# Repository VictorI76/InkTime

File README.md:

# Proiect Hector Watch - nRF52840 Smartwatch

Acest document conține specificațiile tehnice, Bill of Materials (BOM) și detaliile de design pentru proiectul Hector Watch.

---

# 1. Diagramă Bloc

---

# 2. Bill Of Materials (BOM)

| Cant. | Referințe | Valoare | Descriere Tehnică | Producător | Cod Piesă (MPN) |
|:---:|:---|:---|:---|:---|:---|
| 1 | U1 | nRF52840 | Microcontroller Bluetooth LE, AQFN-73 | Nordic Semi | nRF52840-QIAA |
| 1 | IC1 | BQ25180 | Charger Li-Ion/Polymer, 8-DSBGA | Texas Instr. | BQ25180YBGR |
| 1 | IC2 | DRV2605 | Driver Haptic LRA/ERM, 9-DSBGA | Texas Instr. | DRV2605YZFR |
| 1 | IC3 | BMA421 | Accelerometru Triaxial 12-bit | Bosch | BMA423 |
| 1 | IC9 | RT6160 | Buck-Boost DC-DC Controller, 15-WL-CSP | Richtek | RT6160AWSC |
| 1 | U3 | MAX17048 | Fuel Gauge (Monitorizare Baterie) | Maxim/ADI | MAX17048G+T10 |
| 1 | ANT1 | 2.45GHz | Antenă Chip Ceramică | Johanson | 2450AT18B100E |
| 1 | J4 | USB-C | Conector USB Type-C 16 pini | Kinghelm | KH-TYPE-C-16P |
| 1 | J1 | FPC 24 | Conector FFC/FPC 0.5mm, 24 pini  | Molex | 503480-2400 |
| 1 | J2 | TC2030 | Interfață programare Tag-Connect | Tag-Connect | TC2030-IDC |
| 3 | SW_DN, SW_ENT, SW_UP | Tactile | Butoane navigare interfață | Panasonic | EVP-AKE31A |
| 1 | L5 | 68uH | Inductor putere ecranat | Wurth | 744043680 |
| 1 | L4 | 0.47uH | Inductor SMD | TDK | FTC252012SR47MBCA |
| 1 | L2 | 10uH | Inductor generic 0402 | - | - |
| 1 | L3 | 15nH | Inductor generic 0201 | - | - |
| 1 | L1 | 3.9nH | Inductor generic 0201  | - | - |
| 1 | X1 | 32MHz | Cristal cuarț (Main Clock)  | - | - |
| 1 | X2 | 32.768kHz | Cristal cuarț (RTC Clock)  | - | - |
| 3 | D2, D4, D5 | MBR0530 | Diodă Schottky 0.5A, 30V, SOD-123 | ON Semi | MBR0530 |
| 1 | D3 | USBLC6-2 | Protecție ESD USB, SOT-23-6 | ST Micro | USBLC6-2SC6Y |
| 1 | Q1 | P-Ch | Tranzistor P-channel MOSFET | - | - |
| 1 | Q3 | N-Ch | Tranzistor N-channel MOSFET 30V, 1.5A | Vishay | Si1308EDL |
| 6 | R2_EP_DR, R5-R9, R_PWR | 10K | Rezistență 0201 Thin Film | - | - |
| 2 | R1_USB, R2_USB | 5K1 | Rezistență 0201 Thin Film  | - | - |
| 2 | R17, R18 | 3K3 | Rezistență 0201 Thin Film  | - | - |
| 3 | R2, R3, R4 | 0 | Rezistență 0201 (Jumper/0 Ohm) | - | - |
| 6 | C5-C19 | 100nF | Condensator decuplare 0201 | - | - |
| 9 | EPD_C1-C12 | 1uF/50V | Condensator 0402 | - | - |
| 5 | C6, C14, C20, C21, C43 | 4.7uF | Condensator 0402  | - | - |
| 3 | C1-EP-DR, C24, C39 | 10uF | Condensator 0402 | - | - |
| 2 | C25, C33 | 22uF | Condensator 0402 | - | - |
| 4 | C23, C27, C34, C42 | 0.1uF | Condensator 0201 | - | - |
| 4 | C1, C2, C17, C18 | 12pF | Condensator 0201 | - | - |
| 14 | TP_3.3V ... TP_VREG | Test Pad | Puncte de testare semnale | - | - |
| 1 | SJ1 | Solder | Jumper de lipit SMD | - | - |

---

# 3. Funcționalității Hardware

## Descrierea Detaliată a Funcționalității Hardware

Proiectul Hector Watch utilizează o arhitectură modulară optimizată pentru eficiență energetică și dimensiuni reduse, având la bază următoarele componente principale:

### 1. Unitatea Centrală de Procesare (MCU)
* **nRF52840 (U1)**: Acesta este un System-on-Chip (SoC) avansat care rulează logica principală a ceasului și gestionează stack-ul Bluetooth Low Energy.
* **Rol**: Controlează comunicația cu toți senzorii prin magistrala **I2C** și interfața digitală pentru display.

### 2. Managementul Puterii (Power Management)
Sistemul de alimentare este proiectat pentru a asigura stabilitate și longevitate bateriei Li-Ion:
* **Încărcător BQ25180 (IC1)**: Gestionează procesul de încărcare a bateriei via USB și include protecții integrate pentru celula de litiu.
* **Regulator Buck-Boost RT6160 (IC9)**: Un convertor DC-DC care stabilizează tensiunea de sistem la 3.3V, indiferent de variațiile tensiunii bateriei.
* **Monitor Baterie MAX17048 (U3)**: Un circuit de tip "Fuel Gauge" care utilizează algoritmul ModelGauge pentru a raporta precis starea de încărcare a bateriei.

## Analiza Consumului de Energie și Autonomie

Pentru a estima durata de viață a bateriei, am analizat principalele stări de funcționare ale componentelor identificate în BOM:

### 1. Consum pe Module (Estimativ)

| Modul / Componentă | Deep Sleep / Standby | Operare Activă (Typical) |
| :--- | :--- | :--- |
| **nRF52840 (U1)** | ~1.5 µA (RTC ON) | ~4.8 mA |
| **BMA421 (IC3)** | ~1 µA (Suspend) | ~14.5 µA (Low Power) |
| **MAX17048 (U3)** | ~3 µA (Hibernate) | ~23 µA (Activ) |
| **RT6160 (IC9)** | ~1 µA (Iq) | Eficiență >85% |
| **Display E-Paper** | **0 µA** (Static) | ~2-8 mA (Refresh doar) |

### 2. Scenariu de Utilizare Tipic
Consumul mediu este calculat pe baza unui ciclu de funcționare (Duty Cycle) în care dispozitivul petrece 99% din timp în mod Sleep:

* **Consum în Sleep (Sistem complet):** ~20 µA (micro-Amperi).
* **Consum în Activitate (Scurte pulsații):** ~5-10 mA (mili-Amperi).
* **Consum Mediu Estimat:** **~55 µA**.

## Calcul Autonomie
Considerând o baterie Li-Ion standard de **200 mAh**:

$$Autonomie (ore) = \frac{Capacitate (mAh)}{Consum Mediu (mA)}$$

$$Autonomie = \frac{200 mAh}{0.055 mA} \approx 3636 \text{ ore}$$

**Rezultat:** Dispozitivul poate funcționa teoretic aproximativ **5 luni** cu o singură încărcare în regim de standby/notificări ocazionale. Utilizarea intensă a motorului haptic (DRV2605) sau refresh-ul frecvent al ecranului va reduce această perioadă la aproximativ **2-4 săptămâni**.

### 3. Senzori și Feedback Haptic
* **Accelerometru BMA421/BMA423 (IC3)**: Senzor de mișcare triaxial cu consum ultra-redus, utilizat pentru pedometru și detecția gesturilor de ridicare a mâinii.
* **Driver Haptic DRV2605 (IC2)**: Controller specializat pentru motoare de vibrație (ERM/LRA) ce oferă o bibliotecă internă de efecte tactile complexe.

### 4. Interfețe și Comunicație
* **Antenă Chip 2.45GHz (ANT1)**: Componentă ceramică acordată pentru frecvența Bluetooth, esențială pentru conexiunea wireless.
* **Conector FPC J1 (24 pini)**: Interfață de 0.5mm utilizată pentru conectarea panoului de afișaj E-Paper.
* **Port USB Type-C (J4)**: Punctul principal de alimentare și încărcare a dispozitivului.
* **Butoane (SW_UP, SW_DN, SW_ENT)**: Trei switch-uri tactice pentru navigarea utilizatorului în meniurile ceasului.

### 5. Protecție și Componente Pasive
* **Protecție ESD USBLC6-2SC6Y (D3)**: Protejează pinii de date USB împotriva descărcărilor electrostatice.
* **Diodă Schottky MBR0530 (D2, D4, D5)**: Componente utilizate pentru redresare și protecția căilor de alimentare.
* **Filtrare locală**: Sistemul utilizează o rețea densă de condensatoare de decuplare (majoritatea în capsulă 0201) pentru a reduce zgomotul electric pe liniile de alimentare.
---

# 4. Alocare Pini nRF52840

## 1. Alimentare și stabilizare

### Pini implicați

* VDD, VDDH
* DEC1, DEC3, DEC4, DEC5, DEC6
* DCC, DCCHP
* VSS (GND)

### Conectare

* VDD este conectat la 3.3V
* VDDH este conectat la sursa principală (baterie sau regulator)
* Pinii DEC sunt conectați la condensatori (100nF, 1µF, 4.7µF) către masă
* DCC și DCCHP sunt conectați la inductoare pentru convertorul DC/DC

### Motivație

* Asigură stabilitatea tensiunilor interne
* Reduce zgomotul electric
* Permite funcționarea eficientă energetic prin utilizarea convertorului DC/DC intern

---

## 2. Interfața RF (2.4 GHz)

### Pini implicați

* ANT
* VSS_PA

### Conectare

* ANT este conectat la o rețea de adaptare (matching network) formată din inductoare și condensatori
* Rețeaua este conectată la antenă

### Motivație

* Adaptarea impedanței la 50 ohmi
* Maximizarea puterii semnalului emis
* Creșterea sensibilității la recepție

---

## 3. Oscilatoare (ceas)

### Pini implicați

* P0.00 (XL1)
* P0.01 (XL2)
* XC1, XC2

### Conectare

* Cristal de 32.768 kHz cu condensatori de 12pF
* Cristal de 32.768 MHz

### Motivație

* Ceasul de 32 kHz este utilizat pentru RTC și moduri low-power
* Ceasul de mare frecvență este necesar pentru comunicații radio precise

---

## 4. Debug și programare (SWD)

### Pini implicați

* SWDIO
* SWDCLK
* RESET
* SWO (opțional)

### Conectare

* Conectați la un header de programare (TC2030)
* Expuse și prin puncte de test

### Motivație

* Programarea firmware-ului
* Debugging în timpul dezvoltării

---

## 5. Interfață USB

### Pini implicați

* D+
* D-
* VBUS

### Conectare

* Conectați la conector USB-C
* Include protecție ESD

### Motivație

* Comunicație USB cu alte dispozitive
* Posibilitate de alimentare prin USB

---

## 6. Interfață SPI – Display E-Paper

### Pini implicați

* MOSI
* SCK
* EPD_CS
* EPD_DC
* EPD_RST
* EPD_BUSY

### Conectare

* Conectați la conectorul display-ului și circuitul de comandă

### Motivație

* SPI oferă comunicație rapidă
* Liniile suplimentare controlează funcționarea display-ului (comenzi, reset, status)

---

## 7. Interfață I2C

### Pini implicați

* SDA
* SCL

### Conectare

* Conectați la:

  * IMU (accelerometru)
  * Fuel gauge
  * Driver haptic
* Include rezistențe de pull-up (~3.3kΩ)

### Motivație

* Permite conectarea mai multor dispozitive pe aceeași magistrală
* Reduce numărul de pini necesari

---

## 8. GPIO și semnale de întrerupere

### Exemple de semnale

* IMU_INT1, IMU_INT2
* PMIC_INT
* HAPTIC_EN
* Butoane

### Conectare

* Intrări/ieșiri digitale configurabile

### Motivație

* Gestionarea evenimentelor asincrone
* Permite funcționare eficientă energetic (bazată pe întreruperi)

---

## 9. Alimentare externă și baterie

### Conectare

* VBUS → USB
* VBAT → baterie LiPo
* Conectate la:

  * Circuit de încărcare
  * Circuit de monitorizare (fuel gauge)

### Motivație

* Management complet al energiei
* Separarea funcțiilor de alimentare și monitorizare

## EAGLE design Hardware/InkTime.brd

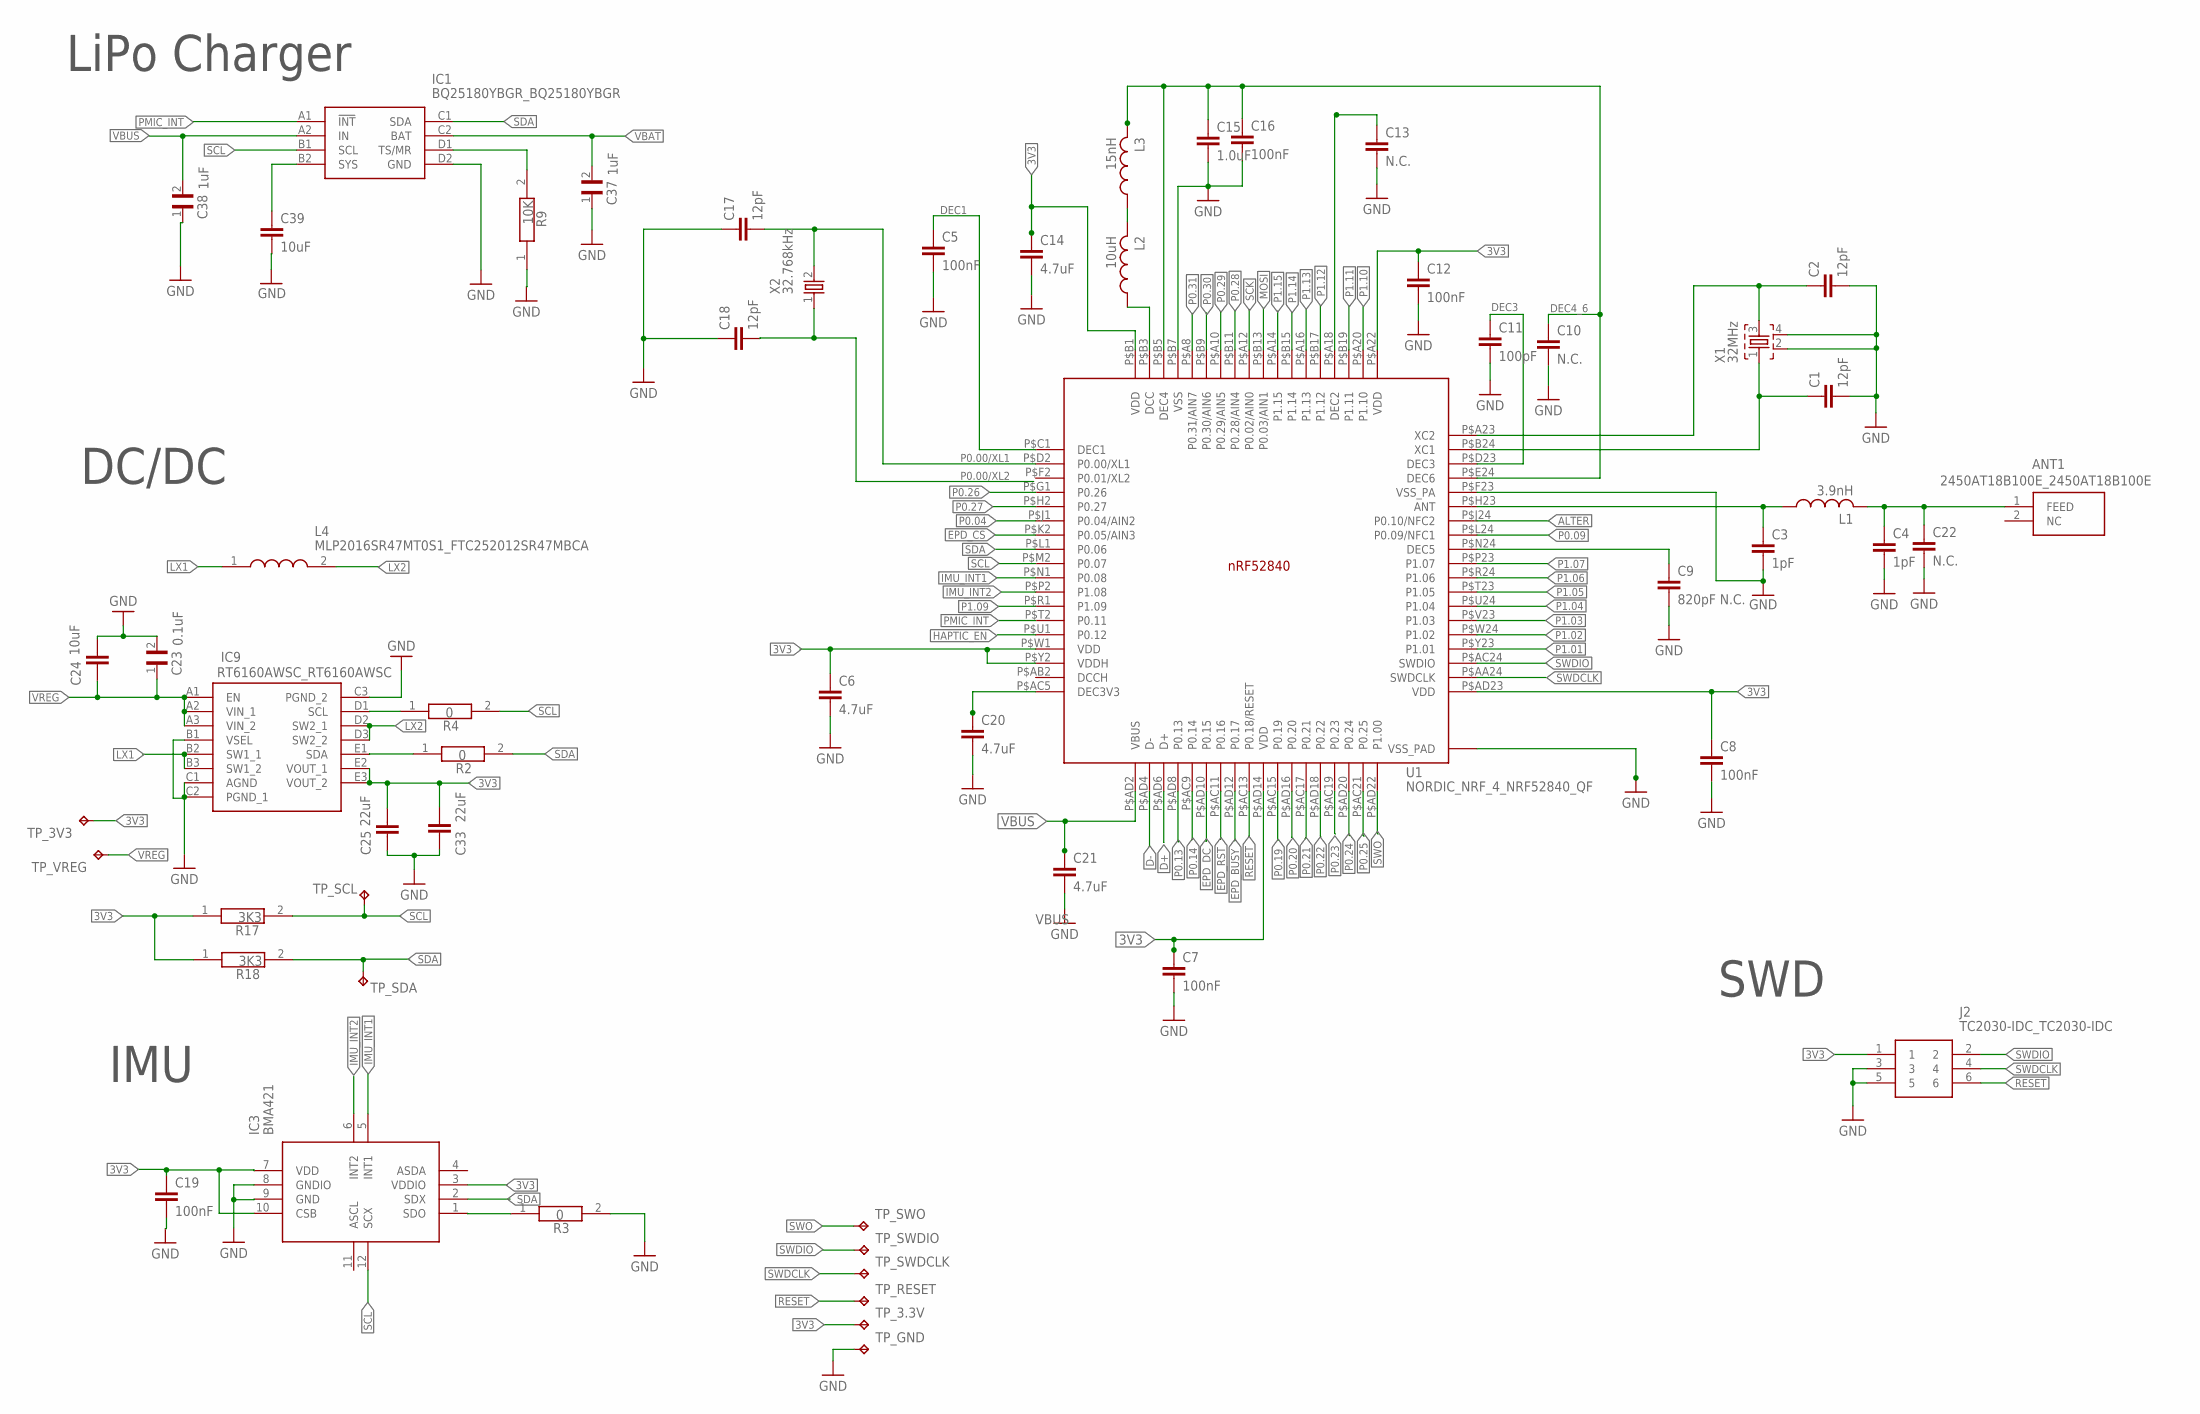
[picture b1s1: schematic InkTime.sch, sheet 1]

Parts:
ANT1: 2450AT18B100E_2450AT18B100E; 2450AT18B100E_ANTC3216X140N
C1, C2, C17, C18: 12pF; NORDIC_NRF_3_RESC0201_N
C3, C4: 1pF; NORDIC_NRF_3_RESC0201_N
C5, C7, C8, C12, C16, C19: 100nF; NORDIC_NRF_3_RESC0201_N
C6, C14, C20, C21: 4.7uF; NORDIC_NRF_3_RESC0402_N
C9: 820pF N.C.; NORDIC_NRF_3_RESC0201_N
C10: N.C.; NORDIC_NRF_3_RESC0402_N
C11: 100pF; NORDIC_NRF_3_RESC0201_N
C13, C22: N.C.; NORDIC_NRF_3_RESC0201_N
C15: 1.0uF; NORDIC_NRF_3_RESC0402_N
C23: 0.1uF; GRM011R60J152KE01L_2_CAPC0201X13N
C24, C39: 10uF; NORDIC_NRF_3_RESC0402_N
C25, C33: 22uF; NORDIC_NRF_3_RESC0402_N
C37, C38: 1uF; GRM011R60J152KE01L_2_CAPC0201X13N
IC1: BQ25180YBGR_BQ25180YBGR; BQ25180YBGR_BGA8C40P2X4_100X155X50
IC3: BMA421; BMA423_BMA423
IC9: RT6160AWSC_RT6160AWSC; RT6160AWSC_BGA15C40P3X5_140X230X60
J2: TC2030-IDC_TC2030-IDC; TC2030-IDC_TC2030IDC
L1: 3.9nH; NORDIC_NRF_2_RESC0201_N
L2: 10uH; NORDIC_NRF_2_RESC0402_N
L3: 15nH; NORDIC_NRF_2_RESC0201_N
L4: MLP2016SR47MT0S1_FTC252012SR47MBCA; MLP2016SR47MT0S1_INDC2016X100N
R2, R3, R4: 0; CPF0201D7K68C1_0201
R9: 10K; CPF0201D7K68C1_0201
R17, R18: 3K3; CPF0201D7K68C1_0201
TP_3.3V, TP_3V3: HECTOR_WATCH_1_TPTP20R; HECTOR_WATCH_1_TP20R
TP_GND: HECTOR_WATCH_1_TPTP20R; HECTOR_WATCH_1_TP20R
TP_RESET: HECTOR_WATCH_1_TPTP20R; HECTOR_WATCH_1_TP20R
TP_SCL: HECTOR_WATCH_1_TPTP20R; HECTOR_WATCH_1_TP20R
TP_SDA: HECTOR_WATCH_1_TPTP20R; HECTOR_WATCH_1_TP20R
TP_SWDCLK: HECTOR_WATCH_1_TPTP20R; HECTOR_WATCH_1_TP20R
TP_SWDIO: HECTOR_WATCH_1_TPTP20R; HECTOR_WATCH_1_TP20R
TP_SWO: HECTOR_WATCH_1_TPTP20R; HECTOR_WATCH_1_TP20R
TP_VREG: HECTOR_WATCH_1_TPTP20R; HECTOR_WATCH_1_TP20R
U1: NORDIC_NRF_4_NRF52840_QF; NORDIC_NRF_4_AQFN50P700X700X85_HS-74N
X1: 32MHz; NORDIC_NRF_BT-XTAL_2016_N
X2: 32.768kHz; NORDIC_NRF_1_XTAL_3215_N

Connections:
3V3: C6.1, C7.1, C8.1, C12.1, C14.1, C19.1, C25.1, C33.1, IC3.3 (VDDIO), IC3.7 (VDD), IC3.10 (CSB), IC9.E2 (VOUT_1), IC9.E3 (VOUT_2), J2.1, R17.1, R18.1, TP_3.3V.TP, TP_3V3.TP, U1.P$A22 (VDD), U1.P$AD14 (VDD), U1.P$AD23 (VDD), U1.P$B1 (VDD), U1.P$W1 (VDD); also elsewhere on the board
ALTER: U1.P$J24 (P0.10/NFC2); also elsewhere on the board
D+: U1.P$AD6 (D+); also elsewhere on the board
D-: U1.P$AD4 (D-); also elsewhere on the board
DEC1: C5.1, U1.P$C1 (DEC1)
DEC2: C13.1, U1.P$A18 (DEC2)
DEC3: C11.1, U1.P$D23 (DEC3)
DEC4_6: C10.1, C15.1, C16.1, L3.2, U1.P$B5 (DEC4), U1.P$E24 (DEC6)
EPD_BUSY: U1.P$AD12 (P0.17); also elsewhere on the board
EPD_CS: U1.P$K2 (P0.05/AIN3); also elsewhere on the board
EPD_DC: U1.P$AD10 (P0.15); also elsewhere on the board
EPD_RST: U1.P$AC11 (P0.16); also elsewhere on the board
GND: C1.2, C2.2, C3.2, C4.2, C5.2, C6.2, C7.2, C8.2, C9.2, C10.2, C11.2, C12.2, C13.2, C14.2, C15.2, C16.2, C17.1, C18.1, C19.2, C20.2, C21.2, C22.2, C23.2, C24.1, C25.2, C33.2, C37.1, C38.1, C39.2, IC1.D2 (GND), IC3.8 (GNDIO), IC3.9 (GND), IC9.B1 (VSEL), IC9.C1 (AGND), IC9.C2 (PGND_1), IC9.C3 (PGND_2), J2.3, J2.5, R3.2, R9.1, TP_GND.TP, U1.P$74 (VSS_PAD), U1.P$75 (VSS_PAD), U1.P$76 (VSS_PAD), U1.P$77 (VSS_PAD), U1.P$78 (VSS_PAD), U1.P$79 (VSS_PAD), U1.P$80 (VSS_PAD), U1.P$81 (VSS_PAD), U1.P$82 (VSS_PAD), U1.P$83 (VSS_PAD), U1.P$84 (VSS_PAD), U1.P$85 (VSS_PAD), U1.P$86 (VSS_PAD), U1.P$87 (VSS_PAD), U1.P$88 (VSS_PAD), U1.P$89 (VSS_PAD), U1.P$90 (VSS_PAD), U1.P$B7 (VSS), U1.P$F23 (VSS_PA), X1.2, X1.4; also elsewhere on the board
HAPTIC_EN: U1.P$U1 (P0.12); also elsewhere on the board
IMU_INT1: IC3.5 (INT1), U1.P$N1 (P0.08)
IMU_INT2: IC3.6 (INT2), U1.P$P2 (P1.08)
LX1: IC9.B2 (SW1_1), IC9.B3 (SW1_2), L4.1
LX2: IC9.D2 (SW2_1), IC9.D3 (SW2_2), L4.2
MOSI: U1.P$B13 (P0.03/AIN1); also elsewhere on the board
unnamed: L2.2, L3.1
unnamed: C20.1, U1.P$AC5 (DEC3V3)
unnamed: L2.1, U1.P$B3 (DCC)
unnamed: C3.1, L1.1, U1.P$H23 (ANT)
unnamed: C9.1, U1.P$N24 (DEC5)
unnamed: C2.1, U1.P$A23 (XC2), X1.3
unnamed: ANT1.1 (FEED), C4.1, C22.1, L1.2
unnamed: C1.1, U1.P$B24 (XC1), X1.1
unnamed: IC9.D1 (SCL), R4.1
unnamed: IC9.E1 (SDA), R2.1
unnamed: C39.1, IC1.B2 (SYS)
unnamed: IC1.D1 (TS/MR), R9.2
unnamed: IC3.1 (SDO), R3.1
P0.00/XL1: C17.2, U1.P$D2 (P0.00/XL1), X2.2
P0.00/XL2: C18.2, X2.1
P0.04: U1.P$J1 (P0.04/AIN2)
P0.09: U1.P$L24 (P0.09/NFC1)
P0.13: U1.P$AD8 (P0.13); also elsewhere on the board
P0.14: U1.P$AC9 (P0.14); also elsewhere on the board
P0.19: U1.P$AC15 (P0.19)
P0.20: U1.P$AD16 (P0.20)
P0.21: U1.P$AC17 (P0.21)
P0.22: U1.P$AD18 (P0.22)
P0.23: U1.P$AC19 (P0.23)
P0.24: U1.P$AD20 (P0.24)
P0.25: U1.P$AC21 (P0.25)
P0.26: U1.P$G1 (P0.26)
P0.27: U1.P$H2 (P0.27)
P0.28: U1.P$B11 (P0.28/AIN4)
P0.29: U1.P$A10 (P0.29/AIN5)
P0.30: U1.P$B9 (P0.30/AIN6)
P0.31: U1.P$A8 (P0.31/AIN7)
P1.01: U1.P$Y23 (P1.01); also elsewhere on the board
P1.02: U1.P$W24 (P1.02); also elsewhere on the board
P1.03: U1.P$V23 (P1.03)
P1.04: U1.P$U24 (P1.04)
P1.05: U1.P$T23 (P1.05)
P1.06: U1.P$R24 (P1.06)
P1.07: U1.P$P23 (P1.07)
P1.09: U1.P$R1 (P1.09)
P1.10: U1.P$A20 (P1.10)
P1.11: U1.P$B19 (P1.11)
P1.12: U1.P$B17 (P1.12)
P1.13: U1.P$A16 (P1.13)
P1.14: U1.P$B15 (P1.14)
P1.15: U1.P$A14 (P1.15)
PMIC_INT: IC1.A1 (!INT), U1.P$T2 (P0.11)
RESET: J2.6, TP_RESET.TP, U1.P$AC13 (P0.18/RESET); also elsewhere on the board
SCK: U1.P$A12 (P0.02/AIN0); also elsewhere on the board
SCL: IC1.B1 (SCL), IC3.12 (SCX), R4.2, R17.2, TP_SCL.TP, U1.P$M2 (P0.07); also elsewhere on the board
SDA: IC1.C1 (SDA), IC3.2 (SDX), R2.2, R18.2, TP_SDA.TP, U1.P$L1 (P0.06); also elsewhere on the board
SWDCLK: J2.4, TP_SWDCLK.TP, U1.P$AA24 (SWDCLK)
SWDIO: J2.2, TP_SWDIO.TP, U1.P$AC24 (SWDIO)
SWO: TP_SWO.TP, U1.P$AD22 (P1.00)
VBAT: C37.2, IC1.C2 (BAT); also elsewhere on the board
VBUS: C21.1, C38.2, IC1.A2 (IN), U1.P$AD2 (VBUS); also elsewhere on the board
VREG: C23.1, C24.2, IC9.A1 (EN), IC9.A2 (VIN_1), IC9.A3 (VIN_2), TP_VREG.TP

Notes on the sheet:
SWD
IMU
DC/DC
LiPo Charger

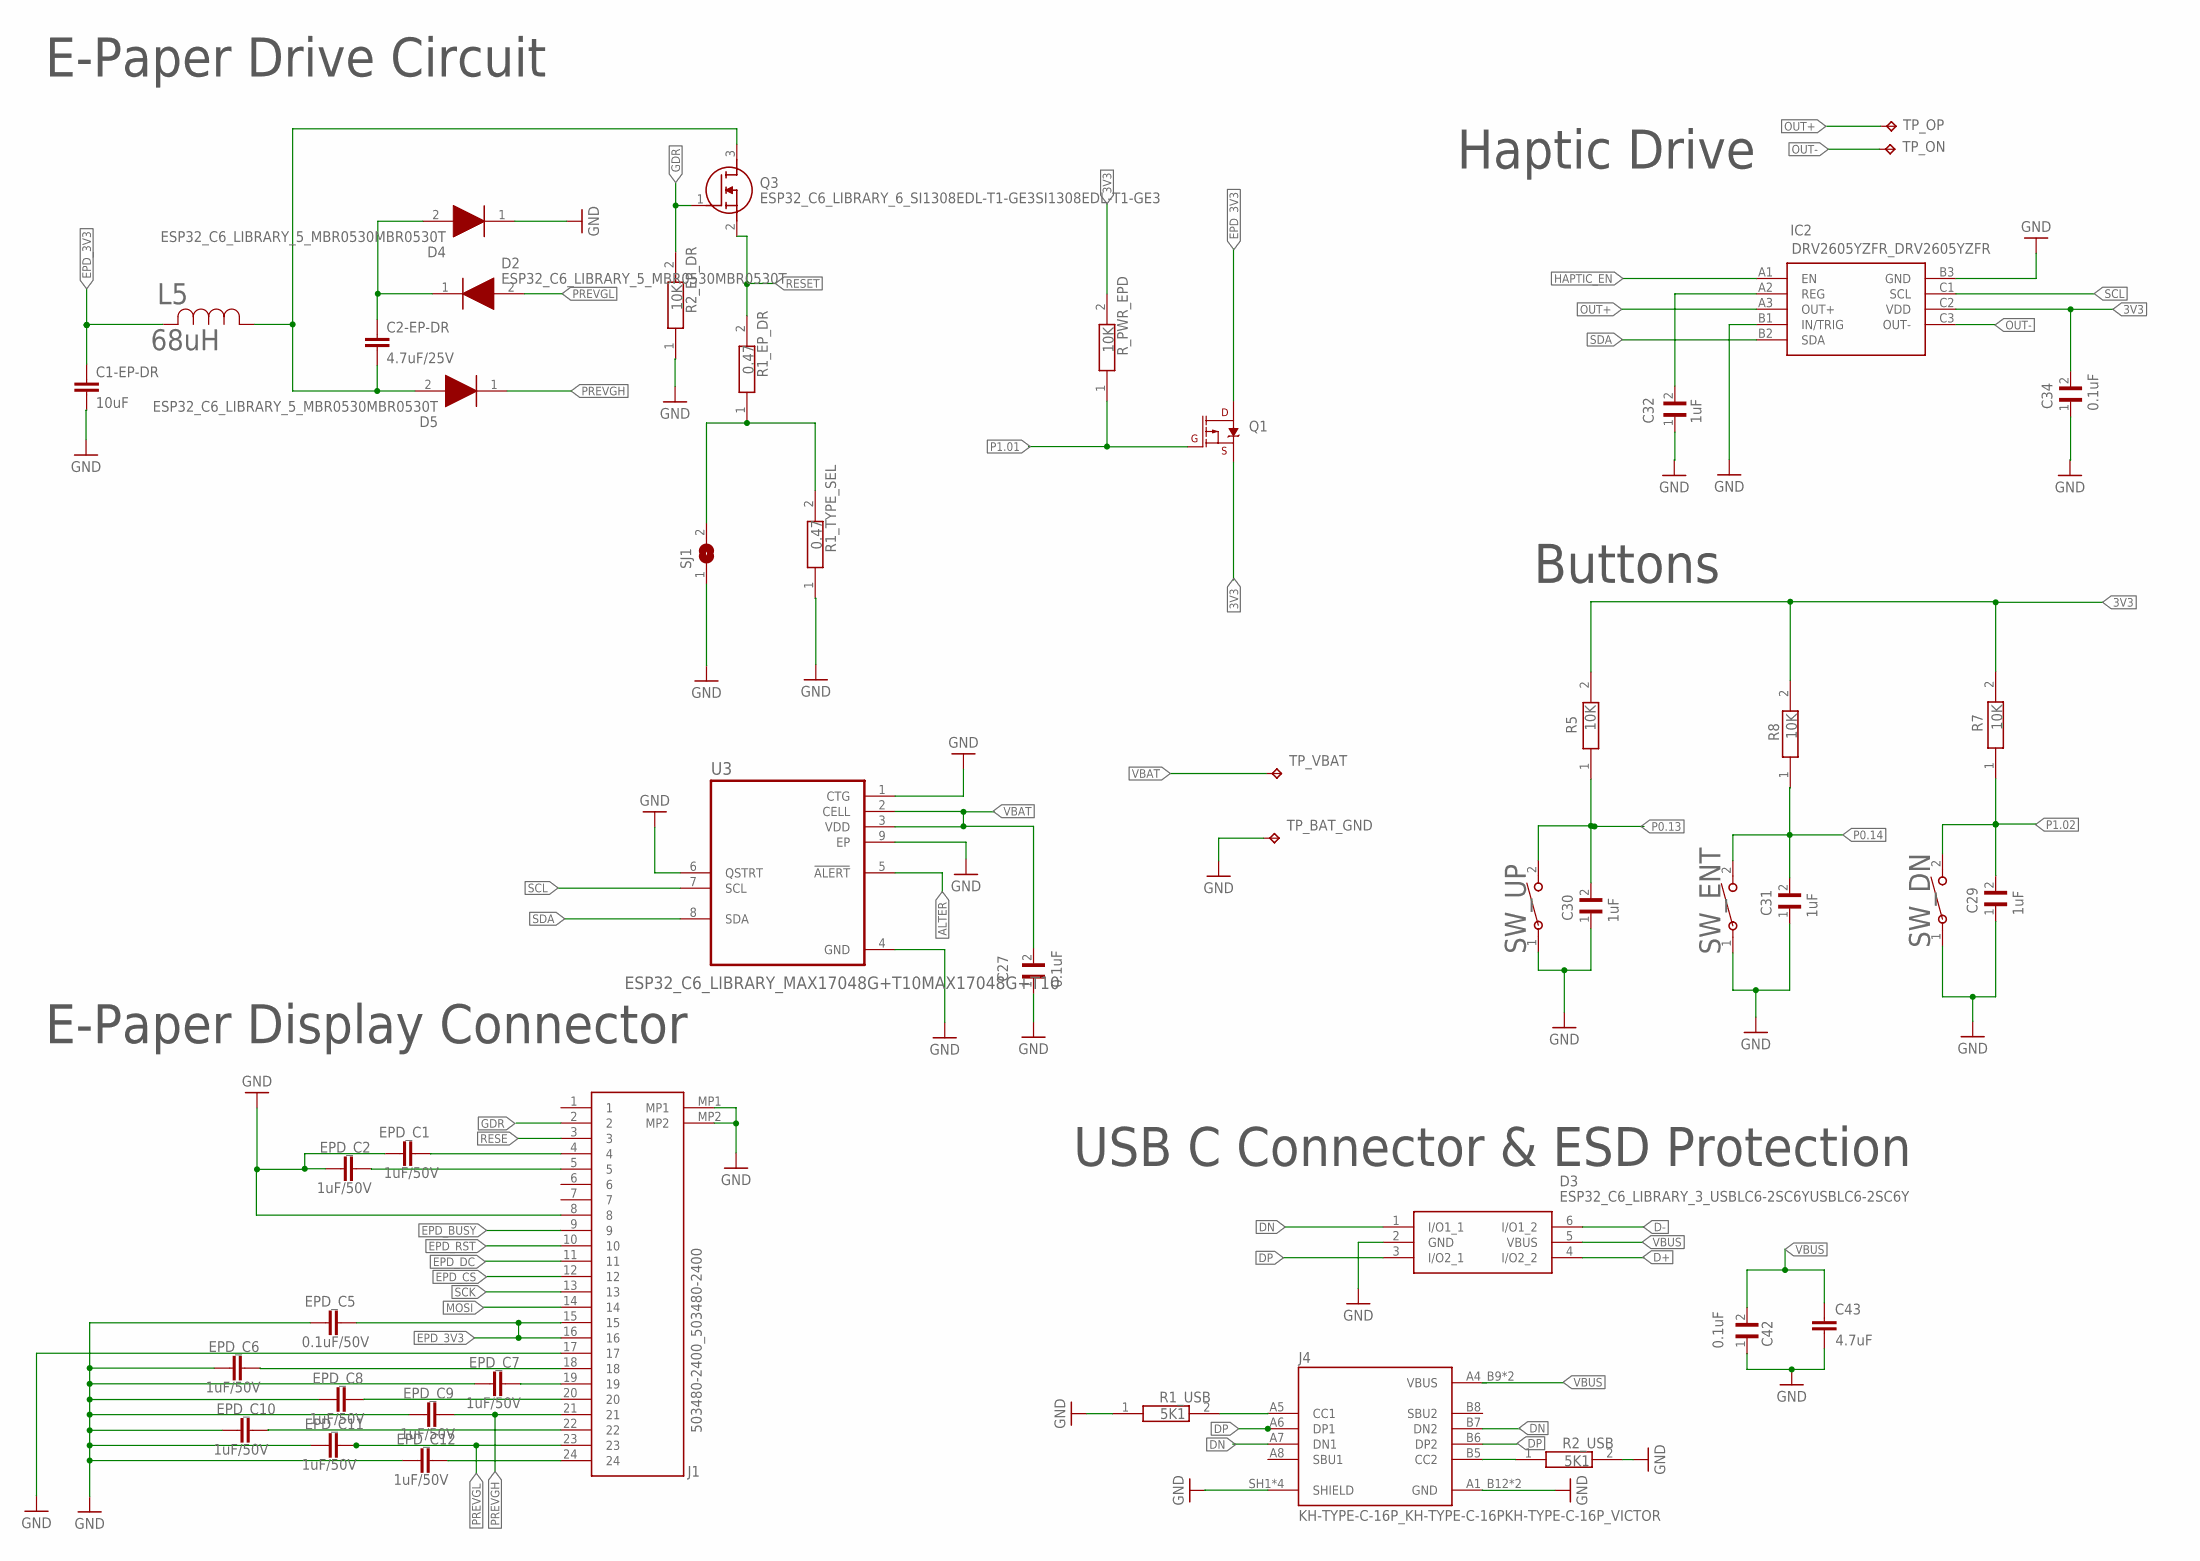
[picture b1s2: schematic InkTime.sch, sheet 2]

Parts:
C1-EP-DR: 10uF; NORDIC_NRF_3_RESC0402_N
C2-EP-DR: 4.7uF/25V; NORDIC_NRF_3_RESC0201_N
C27, C34, C42: 0.1uF; GRM011R60J152KE01L_2_CAPC0201X13N
C29, C30, C31, C32: 1uF; GRM011R60J152KE01L_2_CAPC0201X13N
C43: 4.7uF; NORDIC_NRF_3_RESC0402_N
D2, D4, D5: ESP32_C6_LIBRARY_5_MBR0530MBR0530T; ESP32_C6_LIBRARY_5_SOD3716X135N
D3: ESP32_C6_LIBRARY_3_USBLC6-2SC6YUSBLC6-2SC6Y; ESP32_C6_LIBRARY_3_SOT95P280X145-6N
EPD_C1, EPD_C2, EPD_C6, EPD_C7, EPD_C8, EPD_C9, EPD_C10, EPD_C11, EPD_C12: 1uF/50V; NORDIC_NRF_3_RESC0402_N
EPD_C5: 0.1uF/50V; NORDIC_NRF_3_RESC0402_N
IC2: DRV2605YZFR_DRV2605YZFR; DRV2605YZFR_BGA9C50P3X3_144X144X62
J1: 503480-2400_503480-2400; 503480-2400_5034802400
J4: KH-TYPE-C-16P_KH-TYPE-C-16PKH-TYPE-C-16P_VICTOR; KH-TYPE-C-16P_KINGHELM_KH-TYPE-C-16P
L5: 68uH; ESP32_C6_LIBRARY_2_IND_4828-WE-TPC_WRE
Q1: ESP32_C6_LIBRARY_4_ESP32_WROVER_SPARKFUN-DISCRETE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; ESP32_C6_LIBRARY_4_ESP32_C6_LIBRARY_4_ESP32_C6_LIBRARY_4_ES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
Q3: ESP32_C6_LIBRARY_6_SI1308EDL-T1-GE3SI1308EDL-T1-G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; ESP32_C6_LIBRARY_6_SOT65P210X110-3N
R1_EP_DR, R1_TYPE_SEL: 0.47; CPF0201D7K68C1_0201
R1_USB, R2_USB: 5K1; CPF0201D7K68C1_0201
R2_EP_DR, R5, R7, R8: 10K; CPF0201D7K68C1_0201
R_PWR_EPD: 10K; CPF0201D7K68C1_0201
SJ1: ESP32_C6_LIBRARY_7_JUMPER_SJ
SW_DN: 2025-10-22_07-23-44_LIBRARY_EVP-AKE31A; 2025-10-22_07-23-44_LIBRARY_SW_EVP-AKE31A_PAN
SW_ENT: 2025-10-22_07-23-44_LIBRARY_EVP-AKE31A; 2025-10-22_07-23-44_LIBRARY_SW_EVP-AKE31A_PAN
SW_UP: 2025-10-22_07-23-44_LIBRARY_EVP-AKE31A; 2025-10-22_07-23-44_LIBRARY_SW_EVP-AKE31A_PAN
TP_BAT_GND: HECTOR_WATCH_1_TPTP20R; HECTOR_WATCH_1_TP20R
TP_ON: HECTOR_WATCH_1_TPTP20R; HECTOR_WATCH_1_TP20R
TP_OP: HECTOR_WATCH_1_TPTP20R; HECTOR_WATCH_1_TP20R
TP_VBAT: HECTOR_WATCH_1_TPTP20R; HECTOR_WATCH_1_TP20R
U3: ESP32_C6_LIBRARY_MAX17048G+T10MAX17048G+T10; ESP32_C6_LIBRARY_SON50P200X200X80-9N

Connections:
3V3: C34.2, IC2.C2 (VDD), Q1.2 (S), R5.2, R7.2, R8.2, R_PWR_EPD.2; also elsewhere on the board
ALTER: U3.5 (!ALERT); also elsewhere on the board
D+: D3.4 (I/O2_2); also elsewhere on the board
D-: D3.6 (I/O1_2); also elsewhere on the board
DN: D3.1 (I/O1_1), J4.A7 (DN1), J4.B7 (DN2)
DP: D3.3 (I/O2_1), J4.A6 (DP1), J4.B6 (DP2)
EPD_3V3: C1-EP-DR.1, EPD_C5.1, J1.15, J1.16, L5.2, Q1.3 (D)
EPD_BUSY: J1.9; also elsewhere on the board
EPD_CS: J1.12; also elsewhere on the board
EPD_DC: J1.11; also elsewhere on the board
EPD_RST: J1.10; also elsewhere on the board
GDR: J1.2, Q3.1 (G), R2_EP_DR.2
GND: C1-EP-DR.2, C27.1, C29.1, C30.1, C31.1, C32.1, C34.1, C42.1, C43.1, D3.2 (GND), D4.1 (K), EPD_C1.2, EPD_C2.2, EPD_C5.2, EPD_C6.2, EPD_C7.2, EPD_C8.2, EPD_C9.2, EPD_C10.2, EPD_C11.2, EPD_C12.2, IC2.B1 (IN/TRIG), IC2.B3 (GND), J1.8, J1.17, J1.MP1, J1.MP2, J4.A1_B12 (GND), J4.A12_B1 (GND), J4.SH1 (SHIELD), J4.SH2 (SHIELD), J4.SH3 (SHIELD), J4.SH4 (SHIELD), R1_TYPE_SEL.1, R1_USB.1, R2_EP_DR.1, R2_USB.2, SJ1.1, SW_DN.1, SW_ENT.1, SW_UP.1, TP_BAT_GND.TP, U3.1 (CTG), U3.4 (GND), U3.6 (QSTRT), U3.9 (EP); also elsewhere on the board
HAPTIC_EN: IC2.A1 (EN); also elsewhere on the board
MOSI: J1.14; also elsewhere on the board
unnamed: C2-EP-DR.2, D5.2 (A), L5.1, Q3.3 (D)
unnamed: C2-EP-DR.1, D2.1 (K), D4.2 (A)
unnamed: J4.B5 (CC2), R2_USB.1
unnamed: R1_EP_DR.1, R1_TYPE_SEL.2, SJ1.2
unnamed: J4.A5 (CC1), R1_USB.2
unnamed: C32.2, IC2.A2 (REG)
unnamed: EPD_C1.1, J1.4
unnamed: EPD_C2.1, J1.5
unnamed: EPD_C6.1, J1.18
unnamed: EPD_C7.1, J1.19
unnamed: EPD_C8.1, J1.20
unnamed: EPD_C10.1, J1.22
unnamed: EPD_C12.1, J1.24
OUT+: IC2.A3 (OUT+), TP_OP.TP
OUT-: IC2.C3 (OUT-), TP_ON.TP
P0.13: C30.2, R5.1, SW_UP.2; also elsewhere on the board
P0.14: C31.2, R8.1, SW_ENT.2; also elsewhere on the board
P1.01: Q1.1 (G), R_PWR_EPD.1; also elsewhere on the board
P1.02: C29.2, R7.1, SW_DN.2; also elsewhere on the board
PREVGH: D5.1 (K), EPD_C9.1, J1.21
PREVGL: D2.2 (A), EPD_C11.1, J1.23
RESE: J1.3
RESET: Q3.2 (S), R1_EP_DR.2; also elsewhere on the board
SCK: J1.13; also elsewhere on the board
SCL: IC2.C1 (SCL), U3.7 (SCL); also elsewhere on the board
SDA: IC2.B2 (SDA), U3.8 (SDA); also elsewhere on the board
VBAT: C27.2, TP_VBAT.TP, U3.2 (CELL), U3.3 (VDD); also elsewhere on the board
VBUS: C42.2, C43.2, D3.5 (VBUS), J4.A4_B9 (VBUS), J4.A9_B4 (VBUS); also elsewhere on the board

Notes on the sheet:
E-Paper Drive Circuit
Haptic Drive
Buttons
E-Paper Display Connector
USB C Connector & ESD Protection

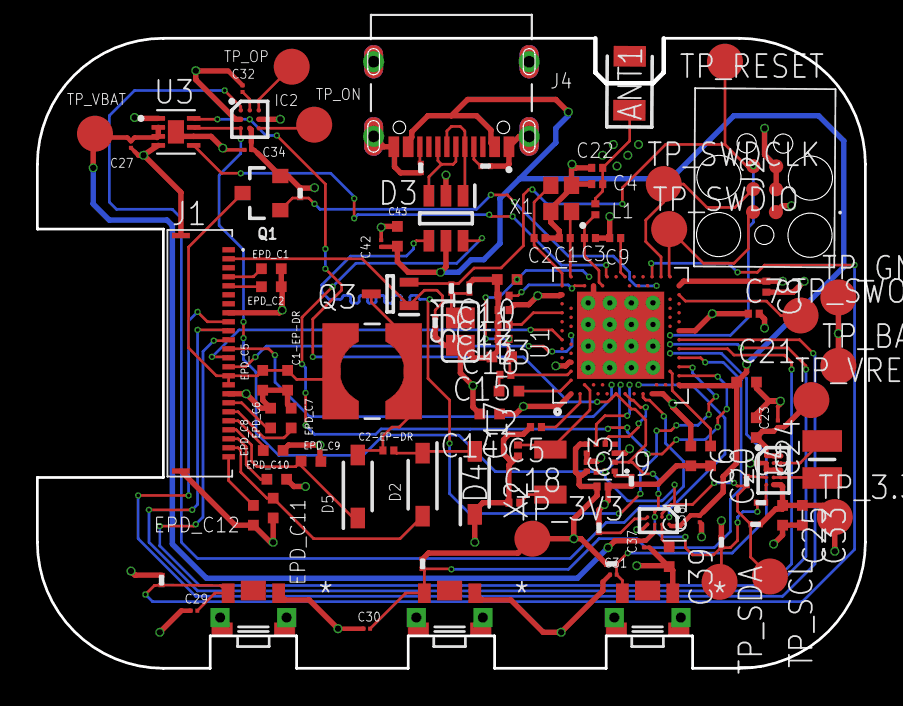
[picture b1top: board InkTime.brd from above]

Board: 4 copper layers, 46.0 x 35.0 mm, 105 parts (0 on the bottom side), 70 nets.

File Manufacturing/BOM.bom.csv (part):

Qty,Value,Device,Package,Parts,Description,ARROW_PART_NUMBER,ARROW_PRICE-STOCK,COPYRIGHT,DESCRIPTION,HEIGHT,JLCPCB,MANUFACTURER_NAME,MANUFACTURER_PART_NUMBER,MFR_NAME,MOUSER_PART_NUMBER,MOUSER_PRICE-STOCK,PACKAGE,POPULARITY,PROD_ID,TP_SIGNAL_NAME
1,,ESP32_C6_LIBRARY_7_JUMPER_SJ,ESP32_C6_LIBRARY_7_JUMPER_SJ,SJ1,"SMD solder JUMPER",,,,,,,,,,,,,3,,
3,0,CPF0201D7K68C1_CPF0201D7K68C1,CPF0201D7K68C1_0201,"R2, R3, R4","7.68k 0201 Thin Film Surface Mount Fixed Resistor +/-0.5% 0.031W CPF0201D7K68C1",,,,,,,,,,,,,,,
4,0.1uF,GRM011R60J152KE01L_2_GRM011R60J152KE01LGRM011R60J152KE01L,GRM011R60J152KE01L_2_CAPC0201X13N,"C23, C27, C34, C42","Check availability",,,,,,,,,,,,,,,
1,0.1uF/50V,NORDIC_NRF_3_CAPACITORCAPACITOR_4020,NORDIC_NRF_3_RESC0402_N,EPD_C5,"Generic chip capacitor",,,,,,,,,,,,,,,
2,0.47,CPF0201D7K68C1_CPF0201D7K68C1,CPF0201D7K68C1_0201,"R1_EP_DR, R1_TYPE_SEL","7.68k 0201 Thin Film Surface Mount Fixed Resistor +/-0.5% 0.031W CPF0201D7K68C1",,,,,,,,,,,,,,,
1,1.0uF,NORDIC_NRF_3_CAPACITORCAPACITOR_4020,NORDIC_NRF_3_RESC0402_N,C15,"Generic chip capacitor",,,,,,,,,,,,,,,
6,100nF,NORDIC_NRF_3_CAPACITOR_0201_N,NORDIC_NRF_3_RESC0201_N,"C5, C7, C8, C12, C16, C19","Generic chip capacitor",,,,,,,,,,,,,,,
1,100pF,NORDIC_NRF_3_CAPACITOR_0201_N,NORDIC_NRF_3_RESC0201_N,C11,"Generic chip capacitor",,,,,,,,,,,,,,,
6,10K,CPF0201D7K68C1_CPF0201D7K68C1,CPF0201D7K68C1_0201,"R2_EP_DR, R5, R7, R8, R9, R_PWR_EPD","7.68k 0201 Thin Film Surface Mount Fixed Resistor +/-0.5% 0.031W CPF0201D7K68C1",,,,,,,,,,,,,,,
3,10uF,NORDIC_NRF_3_CAPACITORCAPACITOR_4020,NORDIC_NRF_3_RESC0402_N,"C1-EP-DR, C24, C39","Generic chip capacitor",,,,,,,,,,,,,,,
1,10uH,NORDIC_NRF_2_INDUCTOR_0402_N,NORDIC_NRF_2_RESC0402_N,L2,"Generic chip inductor",,,,,,,,,,,,,,,
4,12pF,NORDIC_NRF_3_CAPACITOR_0201_N,NORDIC_NRF_3_RESC0201_N,"C1, C2, C17, C18","Generic chip capacitor",,,,,,,,,,,,,,,
1,15nH,NORDIC_NRF_2_INDUCTOR_0201_N,NORDIC_NRF_2_RESC0201_N,L3,"Generic chip inductor",,,,,,,,,,,,,,,
2,1pF,NORDIC_NRF_3_CAPACITOR_0201_N,NORDIC_NRF_3_RESC0201_N,"C3, C4","Generic chip capacitor",,,,,,,,,,,,,,,
6,1uF,GRM011R60J152KE01L_2_GRM011R60J152KE01LGRM011R60J152KE01L,GRM011R60J152KE01L_2_CAPC0201X13N,"C29, C30, C31, C32, C37, C38","Check availability",,,,,,,,,,,,,,,
9,1uF/50V,NORDIC_NRF_3_CAPACITORCAPACITOR_4020,NORDIC_NRF_3_RESC0402_N,"EPD_C1, EPD_C2, EPD_C6, EPD_C7, EPD_C8, EPD_C9, EPD_C10, EPD_C11, EPD_C12","Generic chip capacitor",,,,,,,,,,,,,,,
3,2025-10-22_07-23-44_LIBRARY_EVP-AKE31A,2025-10-22_07-23-44_LIBRARY_EVP-AKE31A,2025-10-22_07-23-44_LIBRARY_SW_EVP-AKE31A_PAN,"SW_DN, SW_ENT, SW_UP",,,,,,,,,,,,,,,,
2,22uF,NORDIC_NRF_3_CAPACITORCAPACITOR_4020,NORDIC_NRF_3_RESC0402_N,"C25, C33","Generic chip capacitor",,,,,,,,,,,,,,,
1,2450AT18B100E_2450AT18B100E,2450AT18B100E_2450AT18B100E,2450AT18B100E_ANTC3216X140N,ANT1,"Antennas 2.45GHz ANTENNA",2450AT18B100E,https://www.arrow.com/en/products/2450at18b100e/johanson-die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,,"Antennas 2.45GHz ANTENNA",1.4mm,,"JOHANSON TECHNOLOGY",2450AT18B100E,,609-2450AT18B100E,https://www.mouser.co.uk/ProductDetail/Johanson-Technology/2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,,,,
1,3.9nH,NORDIC_NRF_2_INDUCTOR_0201_N,NORDIC_NRF_2_RESC0201_N,L1,"Generic chip inductor",,,,,,,,,,,,,,,
1,32.768kHz,NORDIC_NRF_1_XTAL_32KHZ,NORDIC_NRF_1_XTAL_3215_N,X2,,,,,,,,,,,,,,,,
1,32MHz,NORDIC_NRF_XTAL_32MHZ,NORDIC_NRF_BT-XTAL_2016_N,X1,,,,,,,,,,,,,,,,
2,3K3,CPF0201D7K68C1_CPF0201D7K68C1,CPF0201D7K68C1_0201,"R17, R18","7.68k 0201 Thin Film Surface Mount Fixed Resistor +/-0.5% 0.031W CPF0201D7K68C1",,,,,,,,,,,,,,,
5,4.7uF,NORDIC_NRF_3_CAPACITORCAPACITOR_4020,NORDIC_NRF_3_RESC0402_N,"C6, C14, C20, C21, C43","Generic chip capacitor",,,,,,,,,,,,,,,
1,4.7uF/25V,NORDIC_NRF_3_CAPACITOR_0201_N,NORDIC_NRF_3_RESC0201_N,C2-EP-DR,"Generic chip capacitor",,,,,,,,,,,,,,,
1,503480-2400_503480-2400,503480-2400_503480-2400,503480-2400_5034802400,J1,"FFC & FPC Connectors 0.5mm FPC RA SMT Dual Contact 24Ckt",,,,"FFC & FPC Connectors 0.5mm FPC RA SMT Dual Contact 24Ckt",1.87mm,,Molex,503480-2400,,538-503480-2400,https://www.mouser.co.uk/ProductDetail/Molex/503480-2400?qs=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,,,,
2,5K1,CPF0201D7K68C1_CPF0201D7K68C1,CPF0201D7K68C1_0201,"R1_USB, R2_USB","7.68k 0201 Thin Film Surface Mount Fixed Resistor +/-0.5% 0.031W CPF0201D7K68C1",,,,,,,,,,,,,,,
1,68uH,ESP32_C6_LIBRARY_2_744043680IND_4828-WE-TPC_WRE,ESP32_C6_LIBRARY_2_IND_4828-WE-TPC_WRE,L5,,,,"Copyright (C) 2024 Ultra Librarian. All rights reserved.",,,,,744043680,"Wurth Electronics",,,,,,
1,"820pF N.C.",NORDIC_NRF_3_CAPACITOR_0201_N,NORDIC_NRF_3_RESC0201_N,C9,"Generic chip capacitor",,,,,,,,,,,,,,,
1,BMA421,BMA423_BMA423,BMA423_BMA423,IC3,"Accelerometers Triaxial low-g 12bit Acceleration Sensor",BMA423,https://www.arrow.com/en/products/bma423/bosch,,"Accelerometers Triaxial low-g 12bit Acceleration Sensor",1mm,,BOSCH,BMA423,,262-BMA423,https://www.mouser.co.uk/ProductDetail/Bosch-Sensortec/BMA42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,,,,
1,BQ25180YBGR_BQ25180YBGR,BQ25180YBGR_BQ25180YBGR,BQ25180YBGR_BGA8C40P2X4_100X155X50,IC1,"Charger IC Lithium Ion/Polymer, Lithium Iron Phosphate 8-DSBGA (1.6x1.1)",BQ25180YBGR,https://www.arrow.com/en/products/bq25180ybgr/texas-instrume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,,"Charger IC Lithium Ion/Polymer"," Lithium Iron Phosphate 8-DSBGA (1.6x1.1)",0.5mm,,"Texas Instruments",BQ25180YBGR,,595-BQ25180YBGR,https://www.mouser.co.uk/ProductDetail/Texas-Instruments/BQ2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,,,
1,DRV2605YZFR_DRV2605YZFR,DRV2605YZFR_DRV2605YZFR,DRV2605YZFR_BGA9C50P3X3_144X144X62,IC2,"Haptic Driver for ERM/LRA with Built-In Library and Smart Loop Architecture",DRV2605YZFR,https://www.arrow.com/en/products/drv2605yzfr/texas-instrume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,,"Haptic Driver for ERM/LRA with Built-In Library and Smart Loop Architecture",0.625mm,,"Texas Instruments",DRV2605YZFR,,,,,,,
1,ESP32_C6_LIBRARY_3_USBLC6-2SC6YUSBLC6-2SC6Y,ESP32_C6_LIBRARY_3_USBLC6-2SC6YUSBLC6-2SC6Y,ESP32_C6_LIBRARY_3_SOT95P280X145-6N,D3,"Low Cap. ESD Protection Auto SOT-23-6 STMicroelectronics USBLC6-2SC6Y, Dual Uni-Directional TVS Diode Array, 6-Pin SOT-23",,,,,,,,,,,,,,,
1,ESP32_C6_LIBRARY_4_ESP32_WROVER_SPARKFUN-DISCRETESEMI_MOSFET_PCH,ESP32_C6_LIBRARY_4_ESP32_WROVER_SPARKFUN-DISCRETESEMI_MOSFET_PCH,ESP32_C6_LIBRARY_4_ESP32_C6_LIBRARY_4_ESP32_C6_LIBRARY_4_ESP32_C6_LIBRARY_4_ESP32_WROVER_SPARKFUN-DISCRETESEMI_SOT23-3,Q1,"P-channel MOSFETs",,,,,,,,,,,,,,,
3,ESP32_C6_LIBRARY_5_MBR0530MBR0530T,ESP32_C6_LIBRARY_5_MBR0530MBR0530T,ESP32_C6_LIBRARY_5_SOD3716X135N,"D2, D4, D5","ON SEMICONDUCTOR - MBR0530 - DIODE, SCHOTTKY, 0.5A, 30V, SOD-123",,,,,,,,,,,,,,,
1,ESP32_C6_LIBRARY_6_SI1308EDL-T1-GE3SI1308EDL-T1-GE3,ESP32_C6_LIBRARY_6_SI1308EDL-T1-GE3SI1308EDL-T1-GE3,ESP32_C6_LIBRARY_6_SOT65P210X110-3N,Q3,"MOSFET N-Ch 30V 1.5A TrenchFET SC70 Vishay Si1308EDL-T1-GE3 N-channel MOSFET Transistor, 1.5 A, 30 V, 3-Pin SC-70",,,,,,,,,,,,,,,
1,ESP32_C6_LIBRARY_MAX17048G+T10MAX17048G+T10,ESP32_C6_LIBRARY_MAX17048G+T10MAX17048G+T10,ESP32_C6_LIBRARY_SON50P200X200X80-9N,U3,"Check availability",,,,,,,,,,,,,,,
14,HECTOR_WATCH_1_TPTP20R,HECTOR_WATCH_1_TPTP20R,HECTOR_WATCH_1_TP20R,"TP_3.3V, TP_3V3, TP_BAT_GND, TP_GND, TP_ON, TP_OP, TP_RESET, TP_SCL, TP_SDA, TP_SWDCLK, TP_SWDIO, TP_SWO, TP_VBAT, TP_VREG","Test pad",,,,,,,,,,,,,2,,
1,KH-TYPE-C-16P_KH-TYPE-C-16PKH-TYPE-C-16P_VICTOR,KH-TYPE-C-16P_KH-TYPE-C-16PKH-TYPE-C-16P_VICTOR,KH-TYPE-C-16P_KINGHELM_KH-TYPE-C-16P,J4,"Check availability",,,,,,,,,,,,,,,
1,MLP2016SR47MT0S1_FTC252012SR47MBCA,MLP2016SR47MT0S1_FTC252012SR47MBCA,MLP2016SR47MT0S1_INDC2016X100N,L4,"SMD / SMT Inductors (Coils), L=0.47?H, L x W x T :",,,,"SMD / SMT Inductors (Coils)"," L=0.47?H"," L x W x T :",1mm,https://jlcpcb.com/partdetail/6763488-FTC252012SR47MBCA/C5832368,TDK,FTC252012SR47MBCA,,,,,
1,N.C.,NORDIC_NRF_3_CAPACITORCAPACITOR_4020,NORDIC_NRF_3_RESC0402_N,C10,"Generic chip capacitor",,,,,,,,,,,,,,,
2,N.C.,NORDIC_NRF_3_CAPACITOR_0201_N,NORDIC_NRF_3_RESC0201_N,"C13, C22","Generic chip capacitor",,,,,,,,,,,,,,,
1,NORDIC_NRF_4_NRF52840_QF,NORDIC_NRF_4_NRF52840_QF,NORDIC_NRF_4_AQFN50P700X700X85_HS-74N,U1,nRF52840,,,,,,,,,,,,,,,
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
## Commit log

2026-04-08 Rename Readme.md to README.md
2026-04-08 Update README with project details and BOM
2026-04-15 PDF pentru Schematic
2026-04-15 PCB V2

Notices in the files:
parts and their libraries:
COPYRIGHT: Copyright (C) 2024 Ultra Librarian. All rights reserved.
InkTime_v5: COPYRIGHT: Copyright (C) 2025 Ultra Librarian. All rights reserved.
